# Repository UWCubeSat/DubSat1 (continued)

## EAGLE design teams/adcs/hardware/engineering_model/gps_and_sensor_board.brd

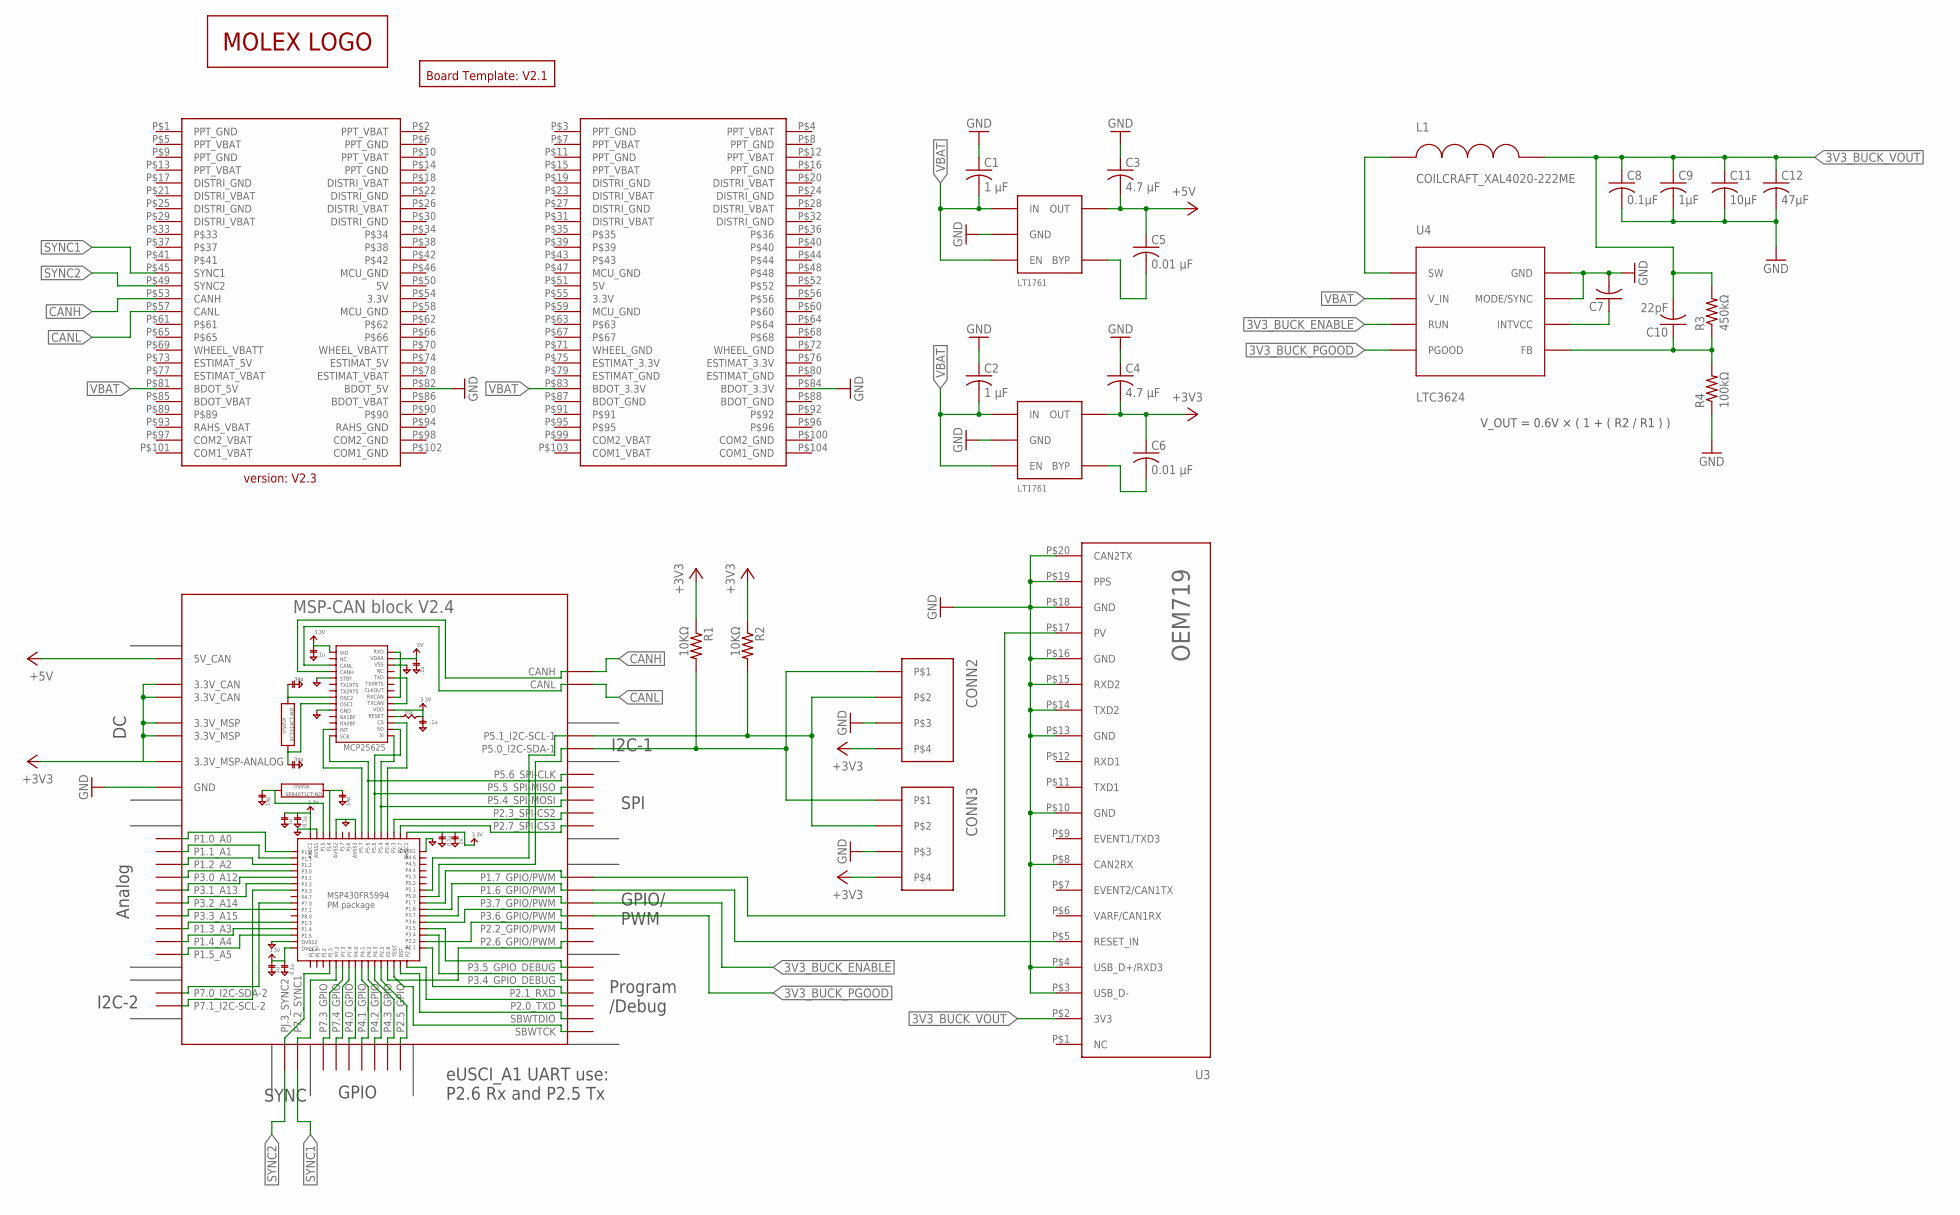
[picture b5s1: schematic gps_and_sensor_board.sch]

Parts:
B1: BOARD_TEMPLATE1; BOARD_TEMPLATE
BLK1: MSP-CAN_BLOCK
C1, C2: 1 μF; C0805
C3, C4: 4.7 μF; C0805
C5, C6: 0.01 μF; C0805
C7: C-USC0805; C0805
C8: 0.1µF; C1206
C9: 1µF; C0805
C10: 22pF; C0805
C11: 10µF; C0805
C12: 47µF; C0805
CONN1: PC104_CONNECTOR
CONN2, CONN3: PICOLOCK_4
L1: COILCRAFT_XAL4020-222ME; COILCRAFT_XAL4020
R1, R2: 10KΩ; R0805
R3: 450kΩ; R0805
R4: 100kΩ; R0805
U1, U2: LINEAR_LDO_LT1761-X; SOT-23-5
U3: OEM719
U4: LTC3624
U$1: LOGO_MOLEX

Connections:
3V3_BUCK_ENABLE: BLK1.P3.7_GPIO/PWM, U4.RUN
3V3_BUCK_FB: C10.1, R3.1, R4.2, U4.FB
3V3_BUCK_INTVCC: C7.1, U4.INTVCC
3V3_BUCK_PGOOD: BLK1.P3.6_GPIO/PWM, U4.PGOOD
3V3_BUCK_SW: L1.P$1, U4.SW
3V3_BUCK_VOUT: C8.1, C9.1, C10.2, C11.1, C12.1, L1.P$2, R3.2, U3.P$2 (3V3)
CANH: BLK1.CANH, CONN1.P$53 (CANH)
CANL: BLK1.CANL, CONN1.P$57 (CANL)
GND: BLK1.GND@1 (GND), BLK1.GND@2 (GND), BLK1.GND@3 (GND), BLK1.GND@4 (GND), BLK1.GND@5 (GND), BLK1.GND@7 (GND), BLK1.GND@8 (GND), BLK1.GND@9 (GND), BLK1.GND@10 (GND), BLK1.GND@11 (GND), BLK1.GND@12 (GND), BLK1.GND@13 (GND), BLK1.GND@14 (GND), BLK1.GND@15 (GND), BLK1.GND@16 (GND), BLK1.GND@17 (GND), BLK1.GND@26 (GND), C1.1, C2.1, C3.1, C4.1, C7.2, C8.2, C9.2, C11.2, C12.2, CONN1.P$82 (BDOT_5V), CONN1.P$84 (BDOT_3.3V), CONN2.P$3, CONN3.P$3, R4.1, U1.P$2 (GND), U2.P$2 (GND), U3.P$3 (USB_D-), U3.P$4 (USB_D+/RXD3), U3.P$8 (CAN2RX), U3.P$10 (GND), U3.P$13 (GND), U3.P$14 (TXD2), U3.P$15 (RXD2), U3.P$16 (GND), U3.P$18 (GND), U3.P$19 (PPS), U3.P$20 (CAN2TX), U4.GND@1 (GND), U4.GND@PAD (GND), U4.MODE/SYNC
GPS_POSITION_VALID: BLK1.P1.7_GPIO/PWM, U3.P$17 (PV)
GPS_RESET_IN: BLK1.P1.6_GPIO/PWM, U3.P$5 (RESET_IN)
I2C_SCL: BLK1.P5.1_I2C-SCL-1, CONN2.P$2, CONN3.P$2, R2.2
I2C_SDA: BLK1.P5.0_I2C-SDA-1, CONN2.P$1, CONN3.P$1, R1.2
LDO_3V3: BLK1.3.3V@CAN1 (3.3V_CAN), BLK1.3.3V@CAN2 (3.3V_CAN), BLK1.3.3V@MSP1 (3.3V_MSP), BLK1.3.3V@MSP2 (3.3V_MSP), BLK1.3.3V_ANALOG@MSP2 (3.3V_MSP-ANALOG), C4.2, C6.1, CONN2.P$4, CONN3.P$4, R1.1, R2.1, U2.P$5 (OUT)
LDO_3V3_BYP: C6.2, U2.P$4 (BYP)
LDO_5V: BLK1.5V (5V_CAN), C3.2, C5.1, U1.P$5 (OUT)
LDO_5V_BYP: C5.2, U1.P$4 (BYP)
SYNC1: BLK1.P7.2_SYNC1, CONN1.P$45 (SYNC1)
SYNC2: BLK1.PJ.3_SYNC2, CONN1.P$49 (SYNC2)
VBAT: C1.2, C2.2, CONN1.P$81 (BDOT_5V), CONN1.P$83 (BDOT_3.3V), U1.P$1 (IN), U1.P$3 (EN), U2.P$1 (IN), U2.P$3 (EN), U4.V_IN

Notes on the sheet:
V_OUT = 0.6V × ( 1 + ( R2 / R1 ) )

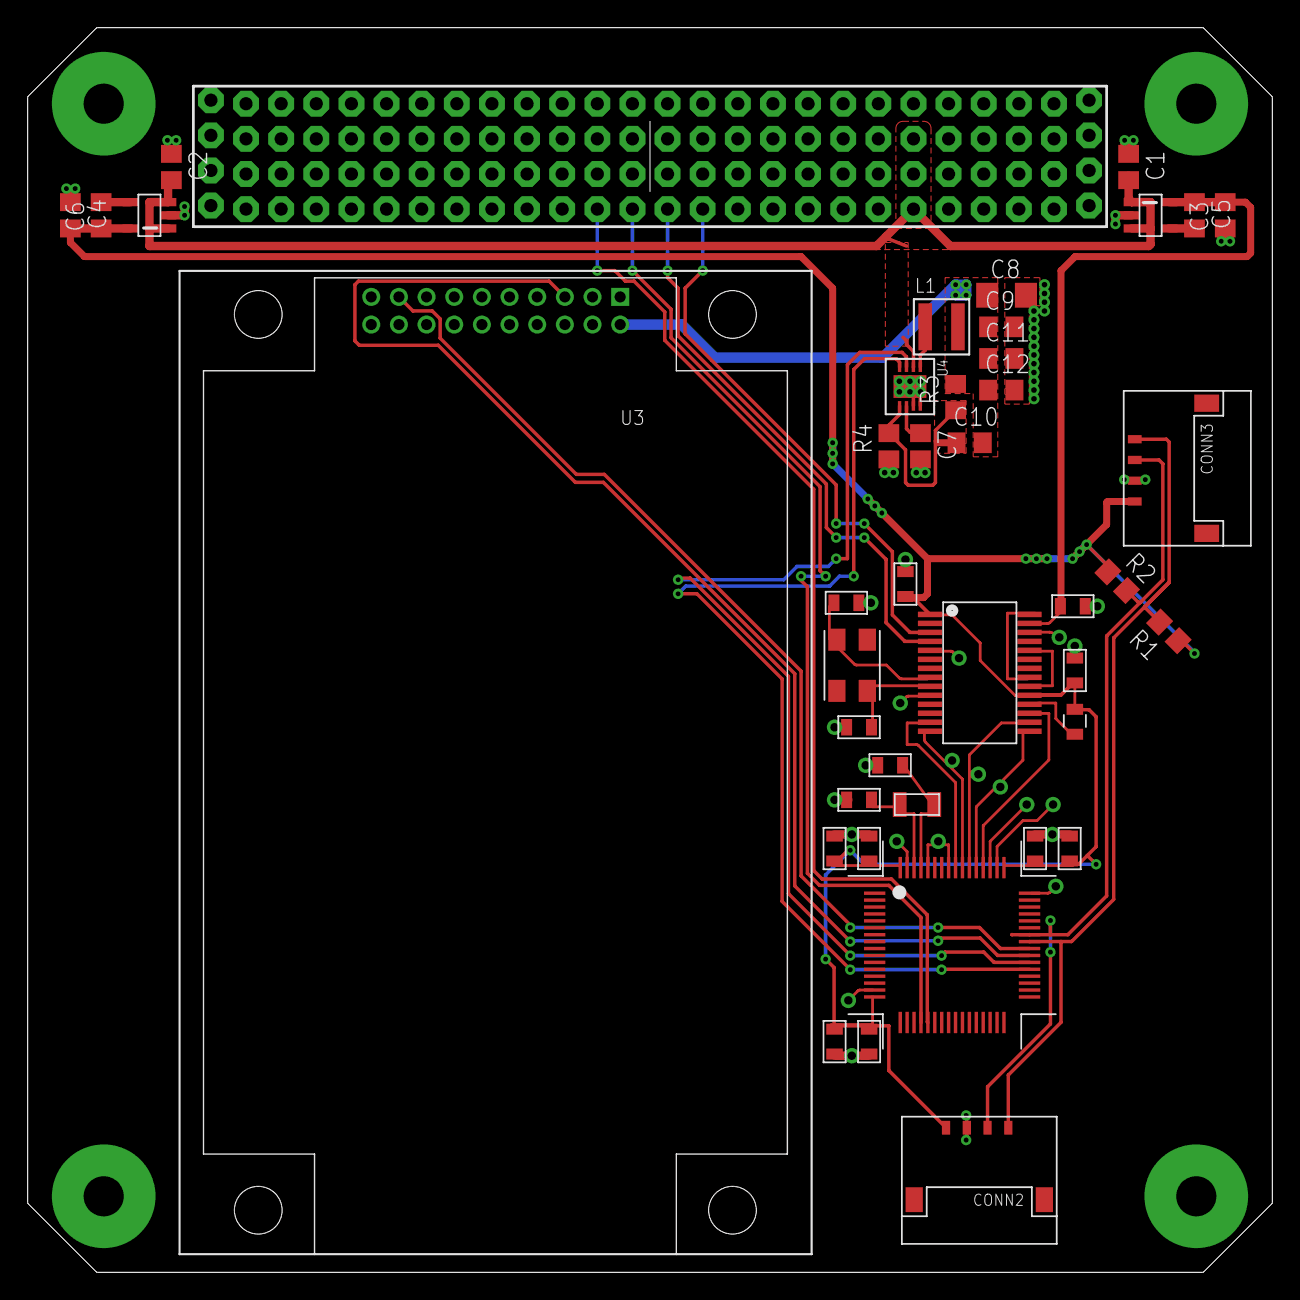
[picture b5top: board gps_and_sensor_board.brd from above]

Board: 2 copper layers, 90.0 x 90.0 mm, 27 parts (1 on the bottom side), 20 nets.
